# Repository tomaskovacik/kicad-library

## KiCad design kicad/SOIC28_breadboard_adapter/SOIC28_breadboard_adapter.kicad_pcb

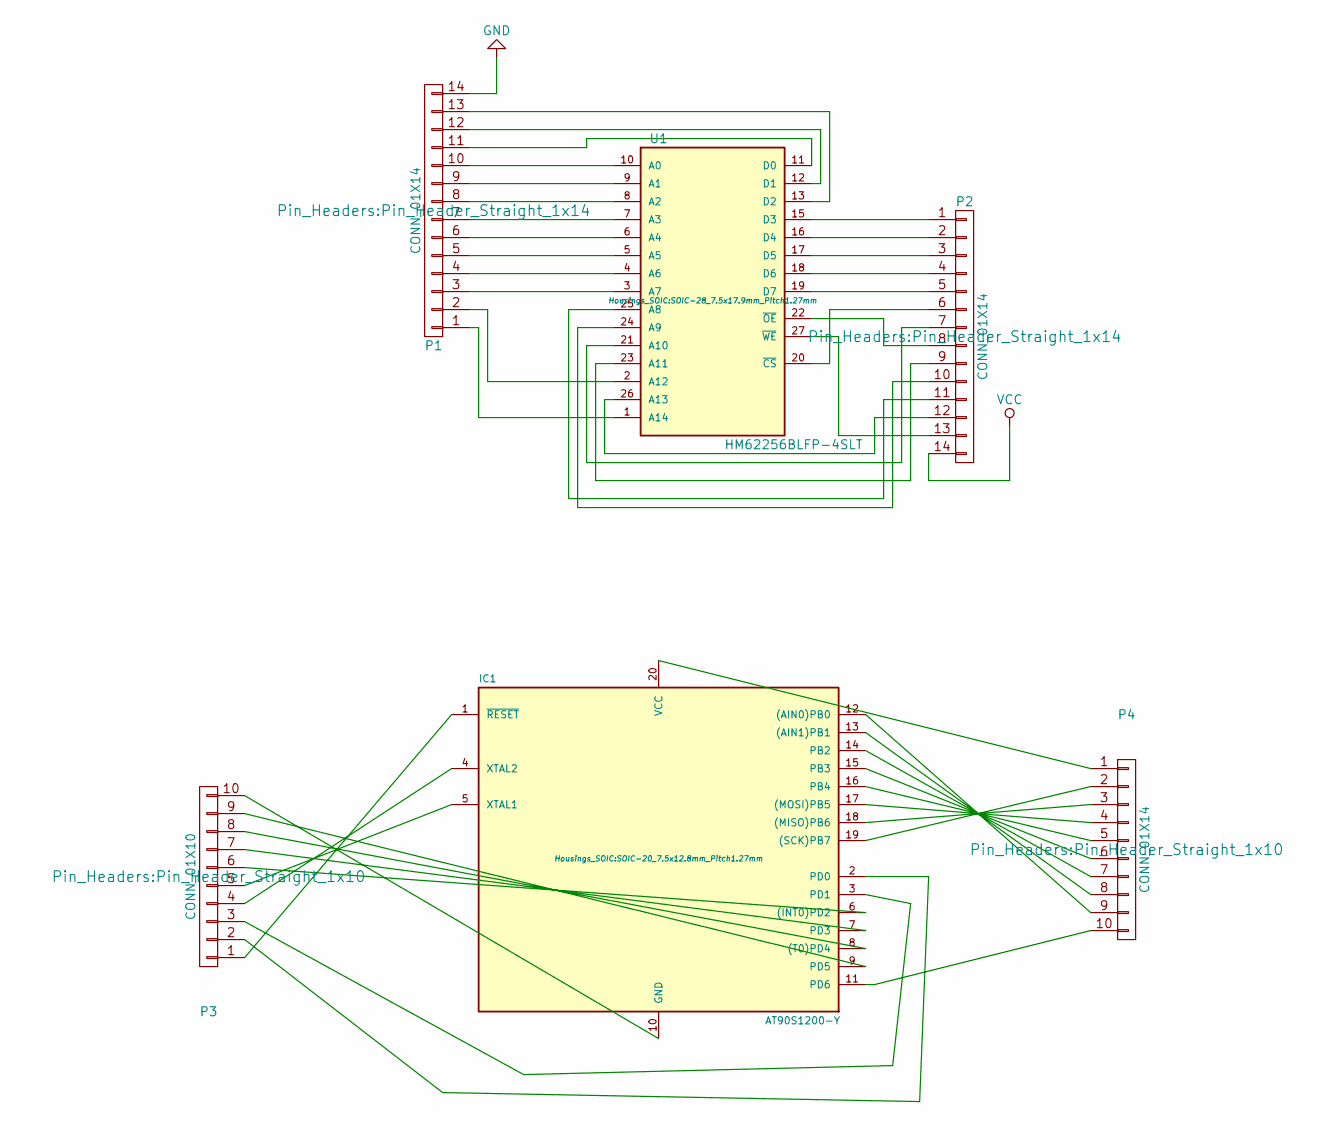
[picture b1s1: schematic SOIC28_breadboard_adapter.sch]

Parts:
IC1: AT90S1200-Y; SOIC-20_7.5x12.8mm_Pitch1.27mm
P1, P2: CONN_01X14; Pin_Header_Straight_1x14
P3: CONN_01X10; Pin_Header_Straight_1x10
P4: CONN_01X14; Pin_Header_Straight_1x10
U1: HM62256BLFP-4SLT; SOIC-28_7.5x17.9mm_Pitch1.27mm

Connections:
GND: P1.14, U1.14 (GND)
unnamed: IC1.1 (~RESET), P3.1
unnamed: IC1.2 (PD0), P3.2
unnamed: IC1.3 (PD1), P3.3
unnamed: IC1.4 (XTAL2), P3.4
unnamed: IC1.5 (XTAL1), P3.5
unnamed: IC1.6 ((INT0)PD2), P3.6
unnamed: IC1.7 (PD3), P3.7
unnamed: IC1.8 ((T0)PD4), P3.8
unnamed: IC1.9 (PD5), P3.9
unnamed: IC1.10 (GND), P3.10
unnamed: IC1.11 (PD6), P4.10
unnamed: IC1.12 ((AIN0)PB0), P4.9
unnamed: IC1.13 ((AIN1)PB1), P4.8
unnamed: IC1.14 (PB2), P4.7
unnamed: IC1.15 (PB3), P4.6
unnamed: IC1.16 (PB4), P4.5
unnamed: IC1.17 ((MOSI)PB5), P4.4
unnamed: IC1.18 ((MISO)PB6), P4.3
unnamed: IC1.19 ((SCK)PB7), P4.2
unnamed: IC1.20 (VCC), P4.1
unnamed: P1.1, U1.1 (A14)
unnamed: P1.2, U1.2 (A12)
unnamed: P1.3, U1.3 (A7)
unnamed: P1.4, U1.4 (A6)
unnamed: P1.5, U1.5 (A5)
unnamed: P1.6, U1.6 (A4)
unnamed: P1.7, U1.7 (A3)
unnamed: P1.8, U1.8 (A2)
unnamed: P1.9, U1.9 (A1)
unnamed: P1.10, U1.10 (A0)
unnamed: P1.11, U1.11 (D0)
unnamed: P1.12, U1.12 (D1)
unnamed: P1.13, U1.13 (D2)
unnamed: P2.1, U1.15 (D3)
unnamed: P2.2, U1.16 (D4)
unnamed: P2.3, U1.17 (D5)
unnamed: P2.4, U1.18 (D6)
unnamed: P2.5, U1.19 (D7)
unnamed: P2.6, U1.20 (~CS)
unnamed: P2.7, U1.21 (A10)
unnamed: P2.8, U1.22 (~OE)
unnamed: P2.9, U1.23 (A11)
unnamed: P2.10, U1.24 (A9)
unnamed: P2.11, U1.25 (A8)
unnamed: P2.12, U1.26 (A13)
unnamed: P2.13, U1.27 (~WE)
VCC: P2.14, U1.28 (VCC)

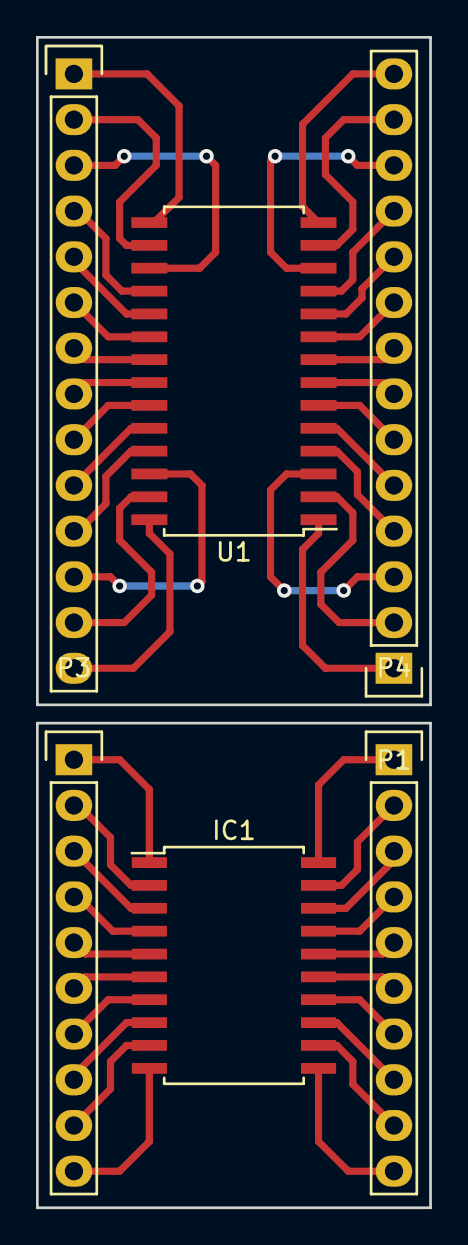
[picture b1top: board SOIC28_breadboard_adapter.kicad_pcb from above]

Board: 2 copper layers, 21.8 x 65.0 mm, 6 parts (0 on the bottom side), 48 nets.

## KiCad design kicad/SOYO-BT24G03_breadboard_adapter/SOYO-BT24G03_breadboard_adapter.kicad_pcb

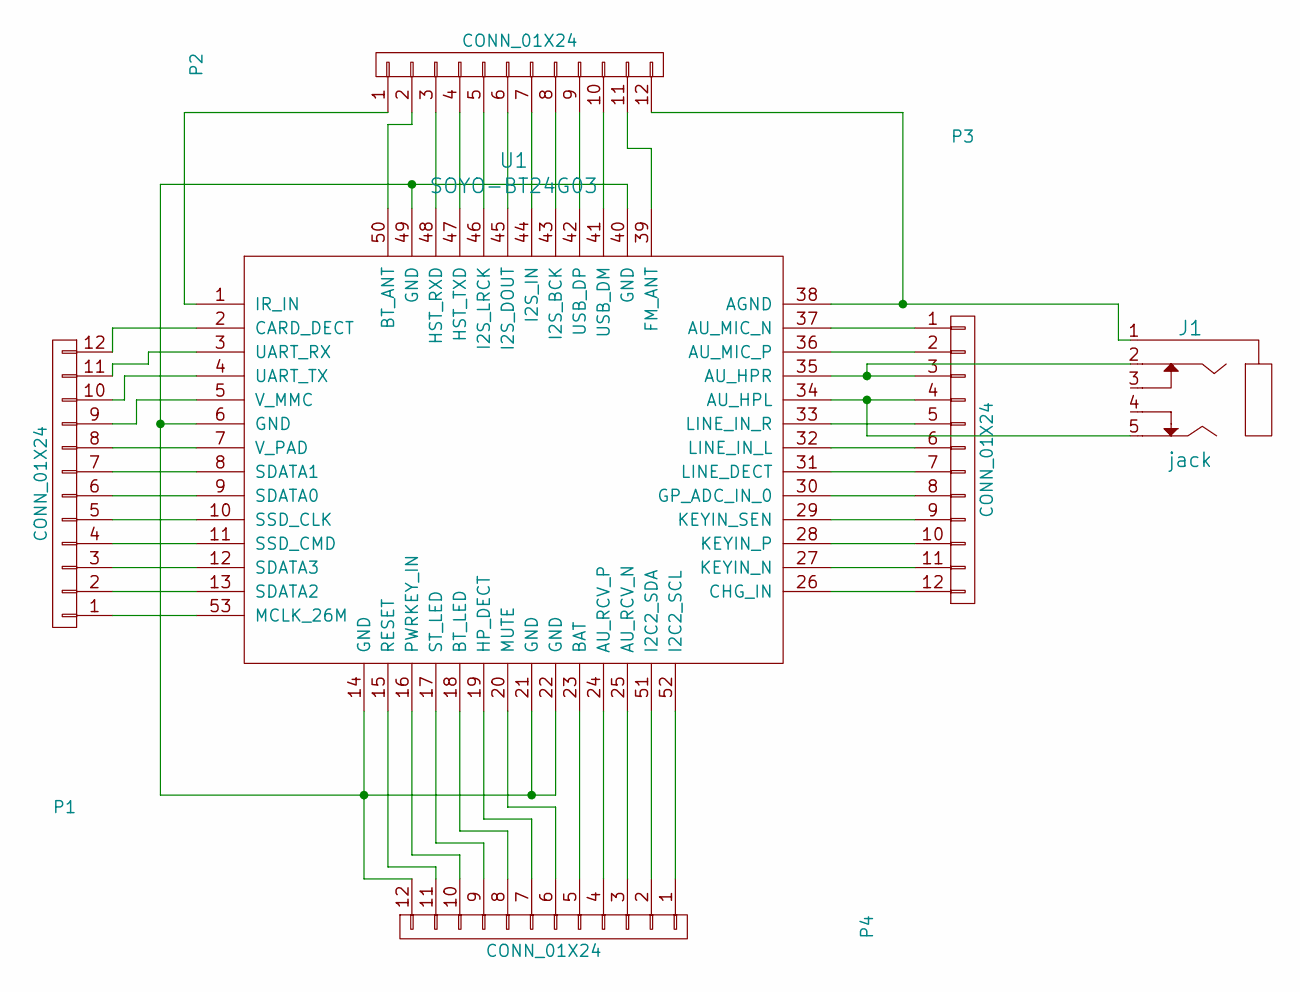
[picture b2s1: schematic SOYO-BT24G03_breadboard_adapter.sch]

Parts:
J1: jack; PJ-327A
P1, P2, P3, P4: CONN_01X24; Pin_Header_Straight_1x12
U1: SOYO-BT24G03

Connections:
unnamed: J1.1, P2.12, U1.38 (AGND)
unnamed: J1.2, P3.3, U1.35 (AU_HPR)
unnamed: J1.5, P3.4, U1.34 (AU_HPL)
unnamed: P1.1, U1.53 (MCLK_26M)
unnamed: P1.2, U1.13 (SDATA2)
unnamed: P1.3, U1.12 (SDATA3)
unnamed: P1.4, U1.11 (SSD_CMD)
unnamed: P1.5, U1.10 (SSD_CLK)
unnamed: P1.6, U1.9 (SDATA0)
unnamed: P1.7, U1.8 (SDATA1)
unnamed: P1.8, U1.7 (V_PAD)
unnamed: P1.9, U1.5 (V_MMC)
unnamed: P1.10, U1.4 (UART_TX)
unnamed: P1.11, U1.3 (UART_RX)
unnamed: P1.12, U1.2 (CARD_DECT)
unnamed: P2.1, U1.1 (IR_IN)
unnamed: P2.2, U1.50 (BT_ANT)
unnamed: P2.3, U1.48 (HST_RXD)
unnamed: P2.4, U1.47 (HST_TXD)
unnamed: P2.5, U1.46 (I2S_LRCK)
unnamed: P2.6, U1.45 (I2S_DOUT)
unnamed: P2.7, U1.44 (I2S_IN)
unnamed: P2.8, U1.43 (I2S_BCK)
unnamed: P2.9, U1.42 (USB_DP)
unnamed: P2.10, U1.41 (USB_DM)
unnamed: P2.11, U1.39 (FM_ANT)
unnamed: P3.1, U1.37 (AU_MIC_N)
unnamed: P3.2, U1.36 (AU_MIC_P)
unnamed: P3.5, U1.33 (LINE_IN_R)
unnamed: P3.6, U1.32 (LINE_IN_L)
unnamed: P3.7, U1.31 (LINE_DECT)
unnamed: P3.8, U1.30 (GP_ADC_IN_0)
unnamed: P3.9, U1.29 (KEYIN_SEN)
unnamed: P3.10, U1.28 (KEYIN_P)
unnamed: P3.11, U1.27 (KEYIN_N)
unnamed: P3.12, U1.26 (CHG_IN)
unnamed: P4.1, U1.52 (I2C2_SCL)
unnamed: P4.2, U1.51 (I2C2_SDA)
unnamed: P4.3, U1.25 (AU_RCV_N)
unnamed: P4.4, U1.24 (AU_RCV_P)
unnamed: P4.5, U1.23 (BAT)
unnamed: P4.6, U1.20 (MUTE)
unnamed: P4.7, U1.19 (HP_DECT)
unnamed: P4.8, U1.18 (BT_LED)
unnamed: P4.9, U1.17 (ST_LED)
unnamed: P4.10, U1.16 (PWRKEY_IN)
unnamed: P4.11, U1.15 (RESET)
unnamed: P4.12, U1.6 (GND), U1.14 (GND), U1.21 (GND), U1.22 (GND), U1.40 (GND), U1.49 (GND)

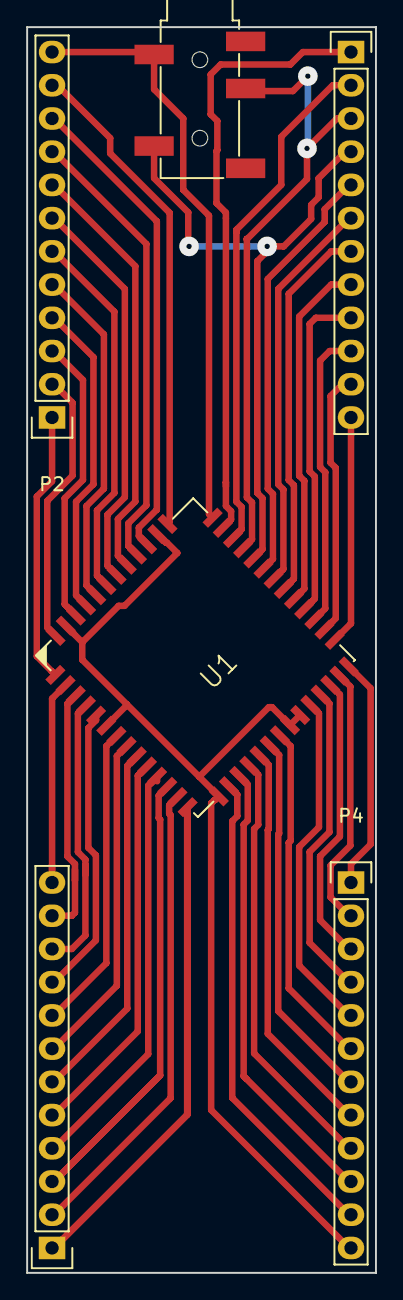
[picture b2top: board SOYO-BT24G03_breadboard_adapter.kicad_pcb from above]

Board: 2 copper layers, 26.7 x 95.2 mm, 6 parts (0 on the bottom side), 48 nets.

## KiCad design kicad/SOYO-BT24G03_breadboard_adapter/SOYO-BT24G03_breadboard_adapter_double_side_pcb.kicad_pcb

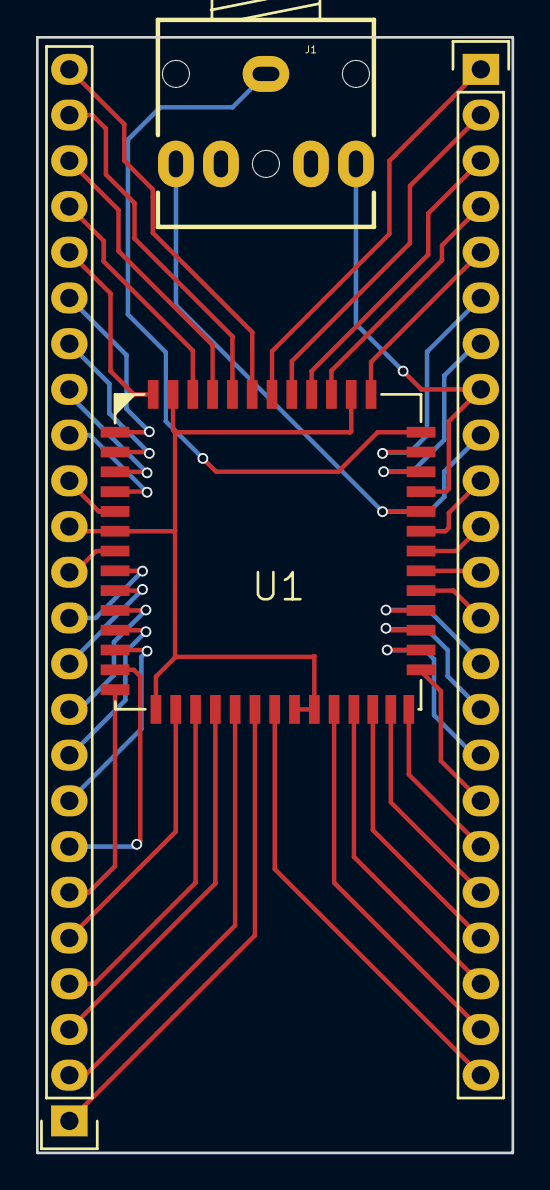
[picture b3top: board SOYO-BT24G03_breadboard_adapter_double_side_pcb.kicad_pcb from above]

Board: 2 copper layers, 26.4 x 62.0 mm, 4 parts (0 on the bottom side), 47 nets.

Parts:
J1: jack; 3.5mm_stereo_jack_PJ306M
P1: CONN_01X24; Pin_Header_Straight_1x24
P2: CONN_01X23; Pin_Header_Straight_1x23
U1: SOYO-BT24G03

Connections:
unnamed: J1.1, P1.14, U1.6, U1.14, U1.21, U1.22, U1.38, U1.40, U1.49
unnamed: J1.2, P2.8, U1.35
unnamed: J1.5, P2.9, U1.34
unnamed: P1.1, U1.19
unnamed: P1.2, U1.18
unnamed: P1.3, U1.17
unnamed: P1.4, U1.16
unnamed: P1.5, U1.15
unnamed: P1.6, U1.53
unnamed: P1.7, U1.13
unnamed: P1.8, U1.12
unnamed: P1.9, U1.11
unnamed: P1.10, U1.10
unnamed: P1.11, U1.9
unnamed: P1.12, U1.8
unnamed: P1.13, U1.7
unnamed: P1.15, U1.5
unnamed: P1.16, U1.4
unnamed: P1.17, U1.3
unnamed: P1.18, U1.2
unnamed: P1.19, U1.1
unnamed: P1.20, U1.50
unnamed: P1.21, U1.48
unnamed: P1.22, U1.47
unnamed: P1.23, U1.46
unnamed: P1.24, U1.45
unnamed: P2.1, U1.44
unnamed: P2.2, U1.43
unnamed: P2.3, U1.42
unnamed: P2.4, U1.41
unnamed: P2.5, U1.39
unnamed: P2.6, U1.37
unnamed: P2.7, U1.36
unnamed: P2.10, U1.33
unnamed: P2.11, U1.32
unnamed: P2.12, U1.31
unnamed: P2.13, U1.30
unnamed: P2.14, U1.29
unnamed: P2.15, U1.28
unnamed: P2.16, U1.27
unnamed: P2.17, U1.26
unnamed: P2.18, U1.52
unnamed: P2.19, U1.51
unnamed: P2.20, U1.25
unnamed: P2.21, U1.24
unnamed: P2.22, U1.23
unnamed: P2.23, U1.20

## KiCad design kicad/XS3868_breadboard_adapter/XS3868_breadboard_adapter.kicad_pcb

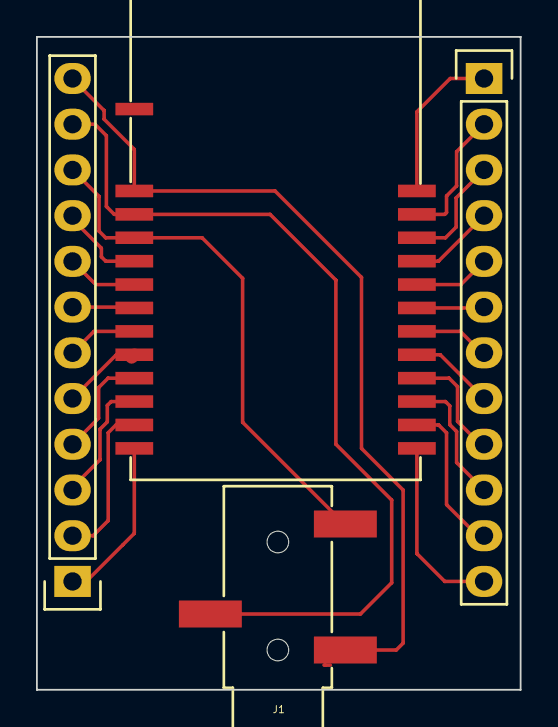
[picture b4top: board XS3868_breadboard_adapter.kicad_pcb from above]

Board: 2 copper layers, 26.9 x 36.3 mm, 4 parts (0 on the bottom side), 24 nets.

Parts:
J1: 3.5mm_stereo_jack_PJ3020B
P1, P2: CONN_01X12; Pin_Header_Straight_1x12
U1: XS3860; XS3868

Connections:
unnamed: J1.1, P1.12, U1.2
unnamed: J1.2, P1.11, U1.3
unnamed: J1.5, P1.10, U1.4
unnamed: P1.1, U1.13
unnamed: P1.2, U1.12
unnamed: P1.3, U1.11
unnamed: P1.4, U1.10
unnamed: P1.5, U1.9
unnamed: P1.6, U1.8
unnamed: P1.7, U1.7
unnamed: P1.8, U1.6
unnamed: P1.9, U1.5
unnamed: P2.1, U1.25
unnamed: P2.2, U1.24
unnamed: P2.3, U1.23
unnamed: P2.4, U1.22
unnamed: P2.5, U1.21
unnamed: P2.6, U1.20
unnamed: P2.7, U1.19
unnamed: P2.8, U1.18
unnamed: P2.9, U1.17
unnamed: P2.10, U1.16
unnamed: P2.11, U1.15
unnamed: P2.12, U1.14

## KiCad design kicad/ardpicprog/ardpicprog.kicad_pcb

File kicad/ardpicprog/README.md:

arduino shield board for http://rweather.github.io/ardpicprog/

status: untested, work in progress

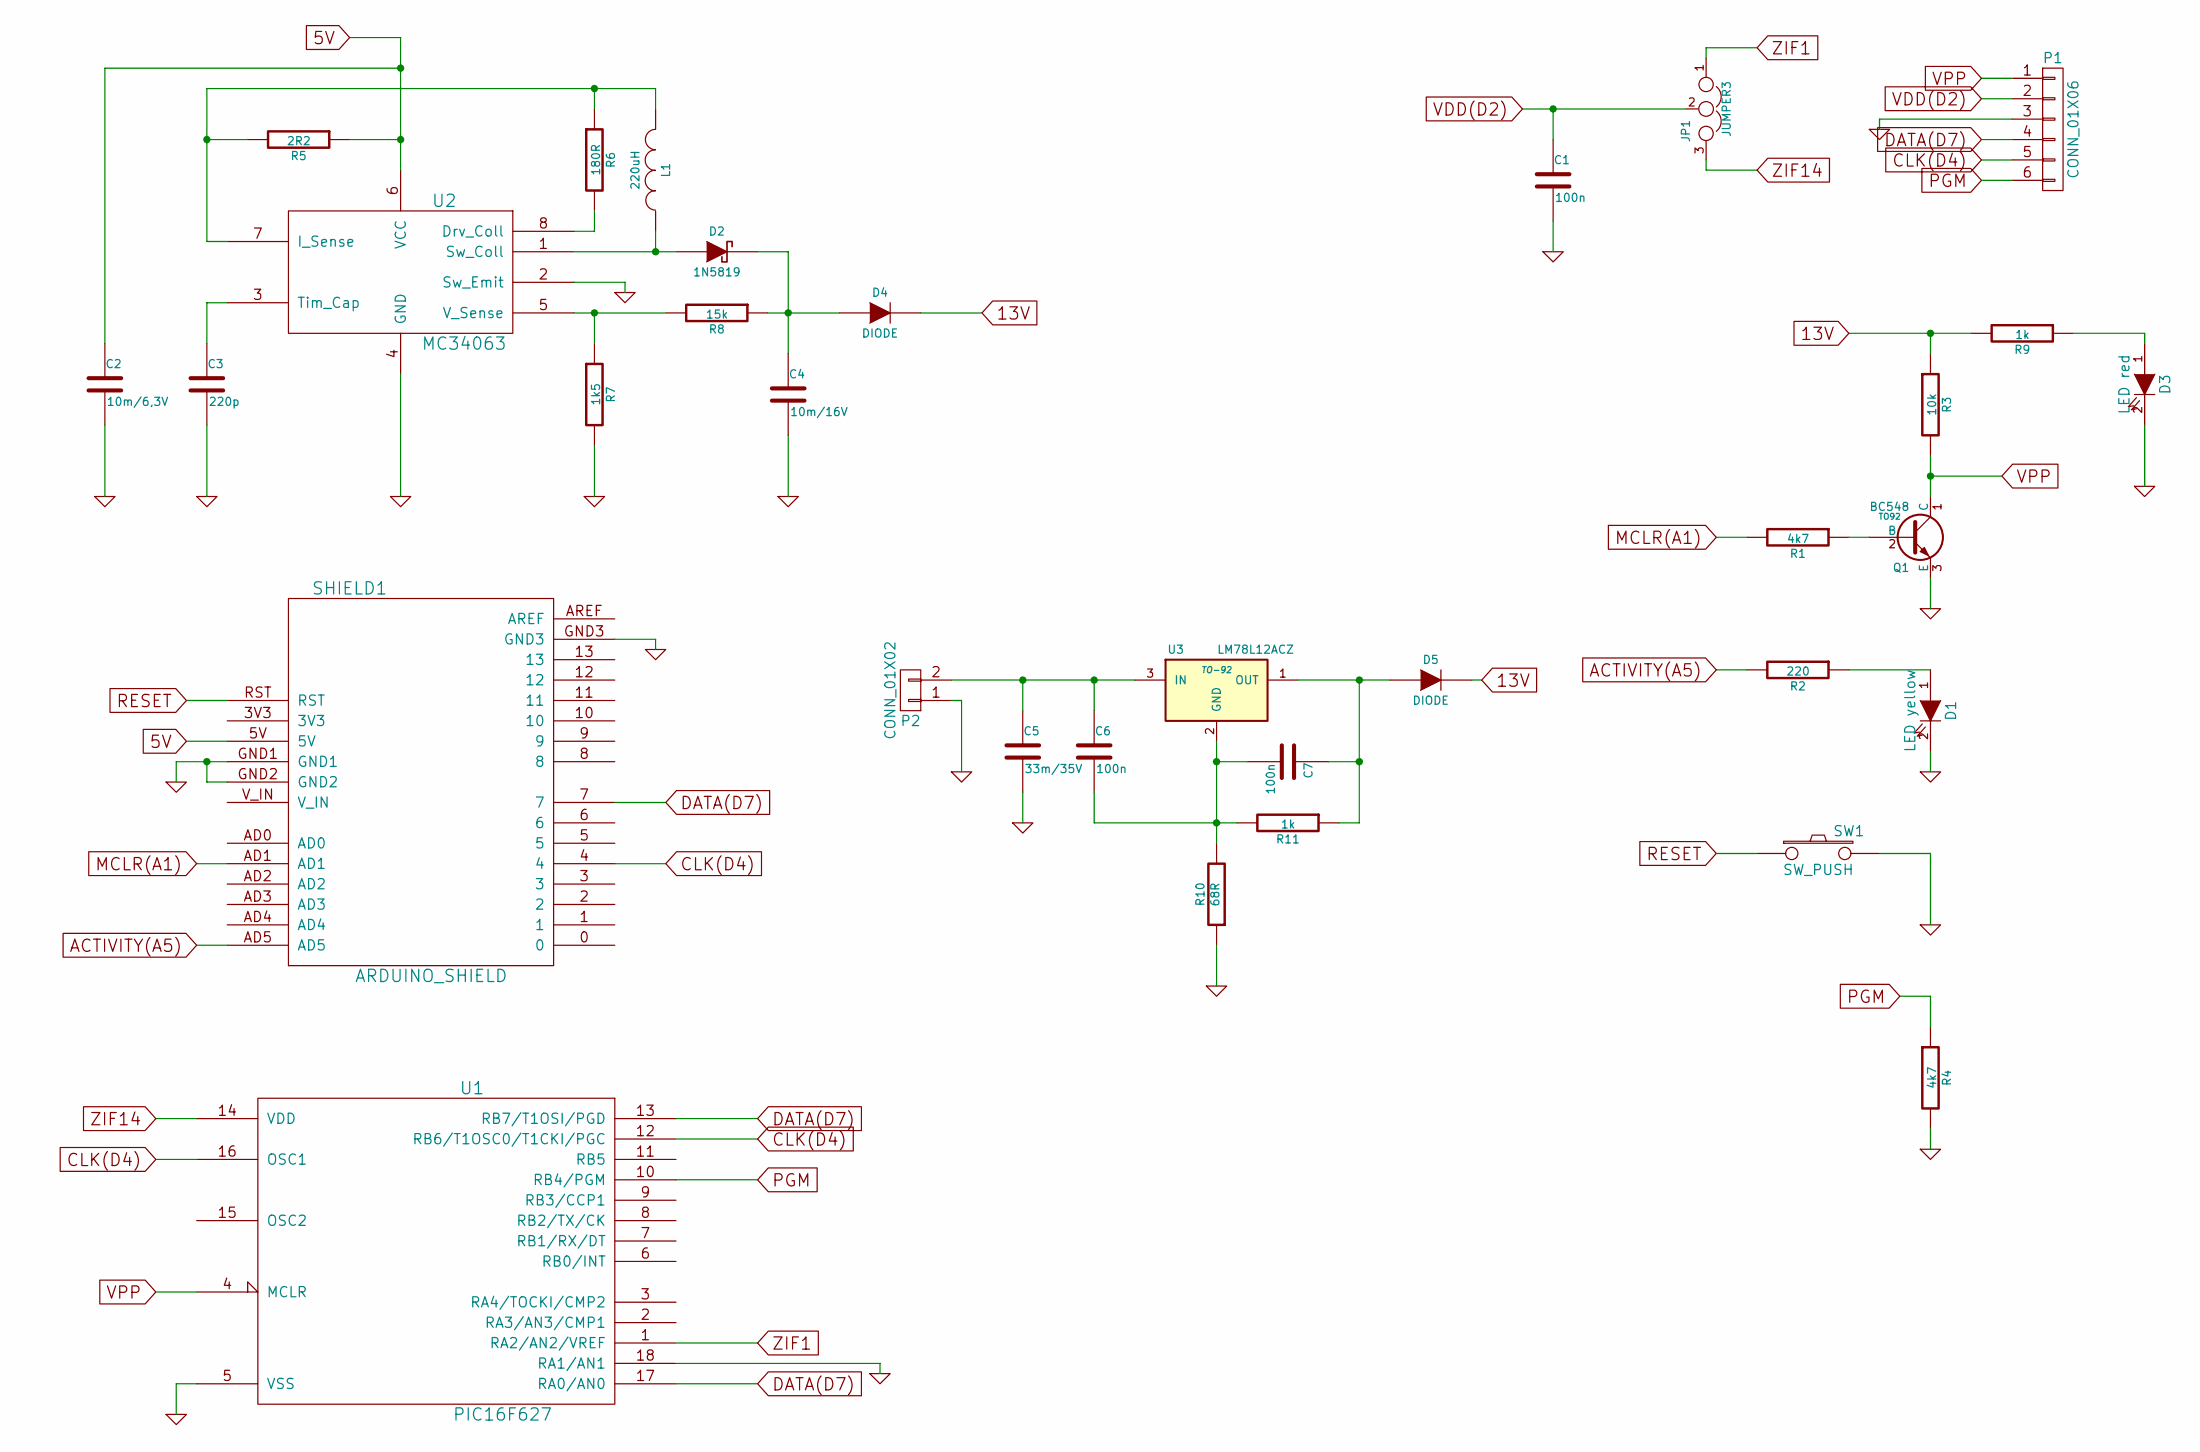
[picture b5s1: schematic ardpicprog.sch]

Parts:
C1, C6, C7: 100n
C2: 10m/6,3V
C3: 220p
C4: 10m/16V
C5: 33m/35V
D1: LED yellow
D2: 1N5819
D3: LED red
D4, D5: DIODE
JP1: JUMPER3
L1: 220uH
P1: CONN_01X06
P2: CONN_01X02
Q1: BC548; TO92
R1, R4: 4k7
R2: 220
R3: 10k
R5: 2R2
R6: 180R
R7: 1k5
R8: 15k
R9, R11: 1k
R10: 68R
SHIELD1: ARDUINO_SHIELD
SW1: SW_PUSH
U1: PIC16F627
U2: MC34063
U3: LM78L12ACZ; TO-92

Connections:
5V: C2.1, R5.1, SHIELD1.5V, U2.6 (VCC)
13V: D4.2 (K), D5.2 (K), R3.1, R9.2
ACTIVITY(A5): R2.2, SHIELD1.AD5
CLK(D4): P1.5, SHIELD1.4, U1.12 (RB6/T1OSC0/T1CKI/PGC), U1.16 (OSC1)
DATA(D7): P1.4, SHIELD1.7, U1.13 (RB7/T1OSI/PGD), U1.17 (RA0/AN0)
GND: C1.2, C2.2, C3.2, C4.2, C5.2, D1.2 (K), D3.2 (K), P1.3, P2.1, Q1.3 (E), R4.2, R7.2, R10.1, SHIELD1.GND1, SHIELD1.GND2, SHIELD1.GND3, SW1.2, U1.5 (VSS), U1.18 (RA1/AN1), U2.2 (Sw_Emit), U2.4 (GND)
MCLR(A1): R1.2, SHIELD1.AD1
unnamed: C3.1, U2.3 (Tim_Cap)
unnamed: C4.1, D2.2 (K), D4.1 (A), R8.1
unnamed: C5.1, C6.1, P2.2, U3.3 (IN)
unnamed: C6.2, C7.2, R10.2, R11.2, U3.2 (GND)
unnamed: C7.1, D5.1 (A), R11.1, U3.1 (OUT)
unnamed: D1.1 (A), R2.1
unnamed: D2.1 (A), L1.1, U2.1 (Sw_Coll)
unnamed: D3.1 (A), R9.1
unnamed: L1.2, R5.2, R6.1, U2.7 (I_Sense)
unnamed: Q1.2 (B), R1.1
unnamed: R6.2, U2.8 (Drv_Coll)
unnamed: R7.1, R8.2, U2.5 (V_Sense)
PGM: P1.6, R4.1, U1.10 (RB4/PGM)
RESET: SHIELD1.RST, SW1.1
VDD(D2): C1.1, JP1.2, P1.2
VPP: P1.1, Q1.1 (C), R3.2, U1.4 (MCLR)
ZIF1: JP1.1, U1.1 (RA2/AN2/VREF)
ZIF14: JP1.3, U1.14 (VDD)

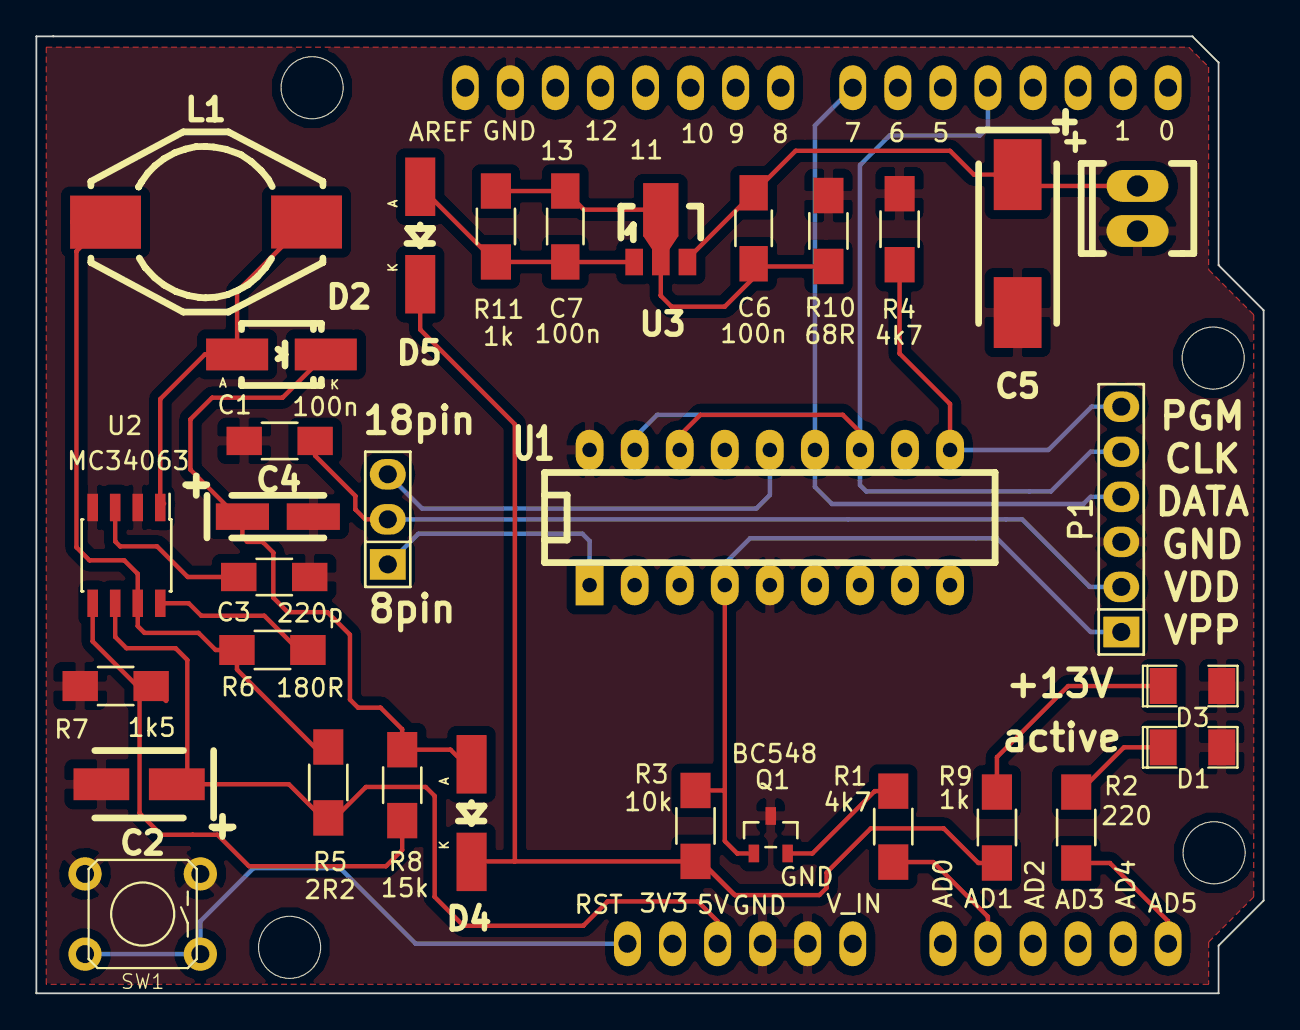
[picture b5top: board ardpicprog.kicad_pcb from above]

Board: 2 copper layers, 69.2 x 53.9 mm, 37 parts (0 on the bottom side), 25 nets.

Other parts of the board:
MH: MountingHole_3-5mm_RevA_Date21Jun2010; MountingHole_3-5mm
MH#2, MH#3, MH#4: MountingHole_3-5mm_RevA_Date21Jun2010; MountingHole_3-5mm
